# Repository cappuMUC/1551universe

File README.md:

1551universe
============

A universal platform for sensor networks and other little helpers in a 40x40 Hammond 1551 case.

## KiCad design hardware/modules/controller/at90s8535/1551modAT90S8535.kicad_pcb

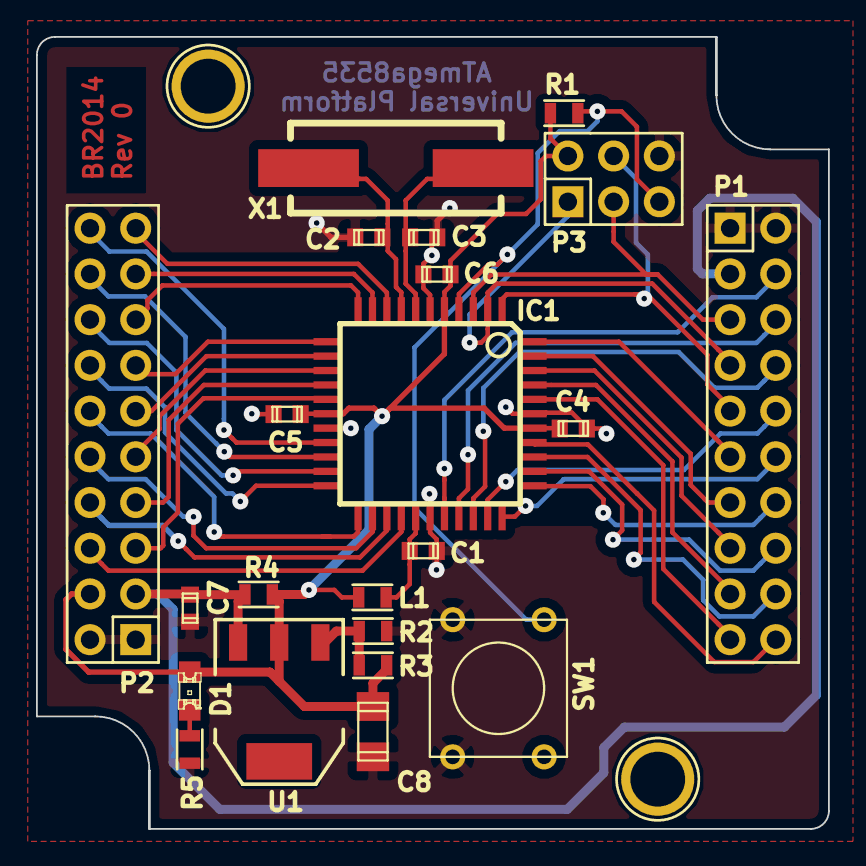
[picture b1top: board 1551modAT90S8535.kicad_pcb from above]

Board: 2 copper layers, 44.0 x 44.0 mm, 24 parts (0 on the bottom side), 42 nets.

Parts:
C1, C4, C5, C6: 100nF; c_0603
C2, C3: C; c_0603
C7: 0,1uF; c_0603
C8: 10uF; c_1206
D1: LED; LED-0805
IC1: ATMEGA8535-A; TQFP-44
L1: 10uH; R_0603
P1, P2: CONN_02X10; Pin_Header_Straight_2x10
P3: CONN_02X03; Pin_Header_Straight_2x03
R1: 10k; R_0603
R2: 680; R_0603
R3: 240; R_0603
R4: 0R; R_0603
R5: 220R; R_0603
SW1: SW_PUSH; SW_PUSH_SMALL
U1: LM317AEMP; SOT-223
X1: CRYSTAL; Crystal_HC49-SD_SMD
X1#2, X2: P***; 1pin

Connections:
/AREF: IC1.29, P1.4
/AVCC: C1.1, IC1.27, L1.1
/PA0: IC1.37, P1.20
/PA1: IC1.36, P1.18
/PA2: IC1.35, P1.16
/PA3: IC1.34, P1.14
/PA4: IC1.33, P1.12
/PA5: IC1.32, P1.10
/PA6: IC1.31, P1.8
/PA7: IC1.30, P1.6
/PB0: IC1.40, P1.19
/PB1: IC1.41, P1.17
/PB2: IC1.42, P1.15
/PB3: IC1.43, P1.13
/PB4: IC1.44, P1.11
/PB5: IC1.1, P1.9, P3.4
/PB6: IC1.2, P1.7, P3.1
/PB7: IC1.3, P1.5, P3.3
/PC0: IC1.19, P2.20
/PC1: IC1.20, P2.18
/PC2: IC1.21, P2.16
/PC3: IC1.22, P2.14
/PC4: IC1.23, P2.12
/PC5: IC1.24, P2.10
/PC6: IC1.25, P2.8
/PC7: IC1.26, P2.6
/PD0: IC1.9, P2.19
/PD1: IC1.10, P2.17
/PD2: IC1.11, P2.15
/PD3: IC1.12, P2.13
/PD4: IC1.13, P2.11
/PD5: IC1.14, P2.9
/PD6: IC1.15, P2.7
/PD7: IC1.16, P2.5
/RESET_N: IC1.4, P3.5, R1.2, SW1.2
/VCC: C4.1, C5.1, C6.1, C8.1, D1.1, IC1.5, IC1.17, IC1.38, L1.2, P2.4, P3.2, R1.1, R3.1, R4.1, U1.2
/V_EXT: C7.1, P1.3, P2.3, R4.2, U1.3
/XTAL_1: C2.2, IC1.8, X1.1
/XTAL_2: C3.2, IC1.7, X1.2
GND: C1.2, C2.1, C3.1, C4.2, C5.2, C6.2, C7.2, C8.2, IC1.6, IC1.18, IC1.28, IC1.39, P1.1, P1.2, P2.1, P2.2, P3.6, R2.2, R5.1, SW1.1
unnamed: D1.2, R5.2
unnamed: R2.1, R3.2, U1.1

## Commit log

2014-11-28 added makefile for AT90S8535 platform
2014-12-17 added the AT90S8535 Control Module Kicad project
2014-12-18 modification on main control pcb
    moved main connectors to fit into an imperial grid
    modified routings to main connector p1
    decreased width of vdd route to connector p2
    added revision to copper text field
2015-02-08 removed controlModule to restructure the folder setup
2015-02-08 added at90s8535 base module in new structure
2015-02-08 added template project for new 1551 shields and controllers
    The template is derived from the at90s8535 controller board.
    There could be some old at90 stuff left inside the template.
2015-05-14 added libraries to repository
2015-05-14 modified target in makefile
